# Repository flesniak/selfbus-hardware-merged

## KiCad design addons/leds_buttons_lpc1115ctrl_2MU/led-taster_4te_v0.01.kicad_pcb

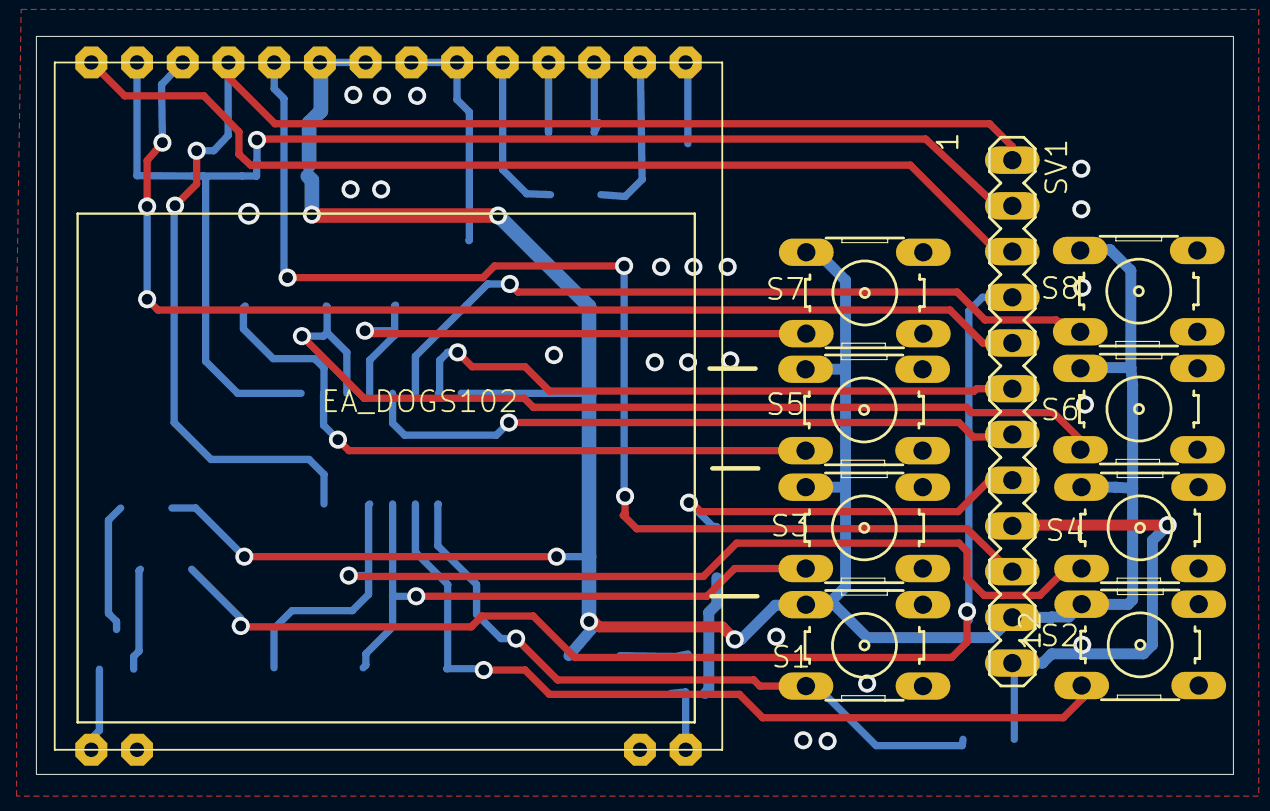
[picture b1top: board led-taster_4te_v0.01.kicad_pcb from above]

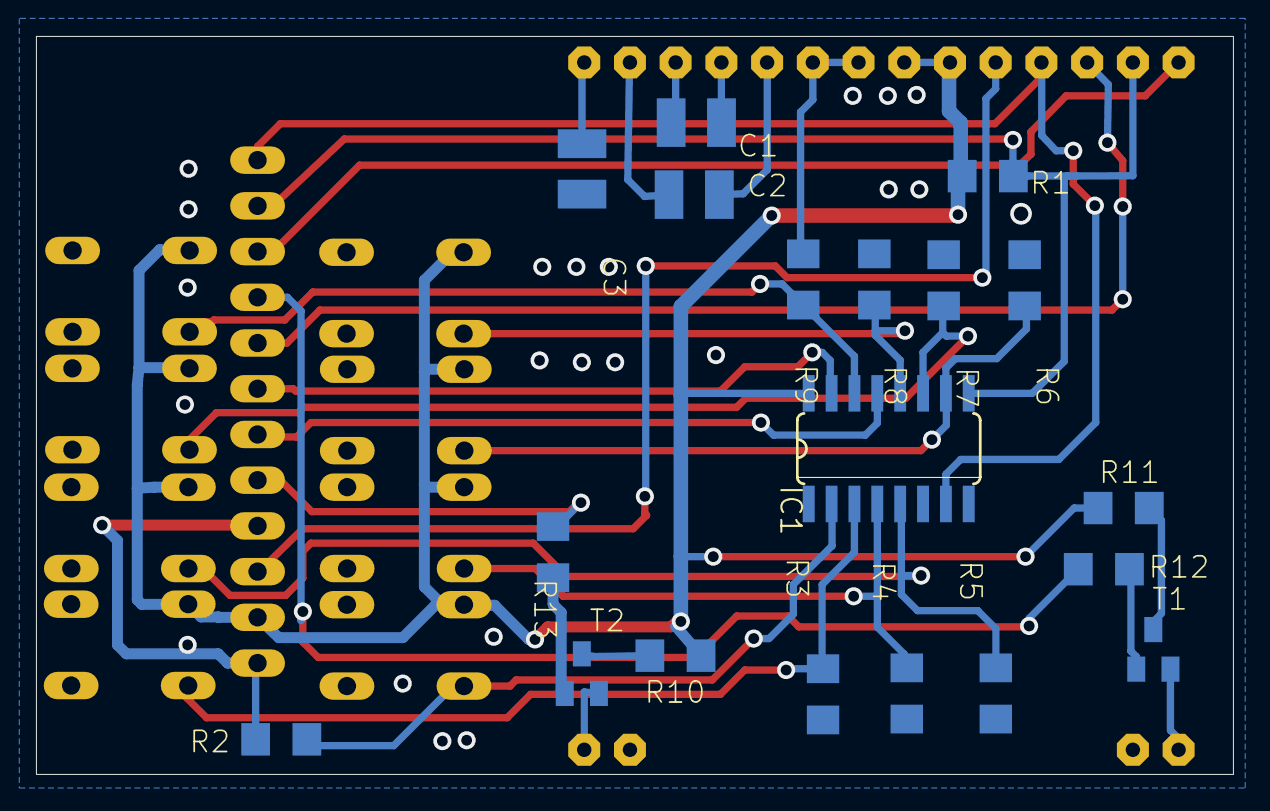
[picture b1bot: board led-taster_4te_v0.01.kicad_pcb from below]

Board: 2 copper layers, 66.5 x 41.0 mm, 29 parts (19 on the bottom side), 30 nets.

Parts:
C1, C2, C3: 1µ; C1210
EA_DOGS102: DOGS102
IC1: 74HC166D; SO16
R1, R2, R3, R4, R5, R6, R7, R8, R9: 10k; R1206
R10, R11: R1206
R12, R13: 1k; R1206
S1, S2, S3, S4, S5, S6, S7, S8: B3F-10XX
SV1: MA12-1
T1, T2: BC847; SOT23

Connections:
+3V3: EA_DOGS102.22, EA_DOGS102.23, IC1.16, R1.2, R10.1, R11.1, S1.1, S2.1, S3.1, S4.1, S5.1, S6.1, S7.1, S8.1, SV1.11
GND: C3.1, EA_DOGS102.2, EA_DOGS102.13, EA_DOGS102.20, EA_DOGS102.21, IC1.1, IC1.6, IC1.8, R2.2, R3.2, R4.2, R5.2, R6.2, R7.2, R8.2, R9.2, SV1.9, SV1.12
MISO: IC1.13, SV1.7
MOSI: EA_DOGS102.24, SV1.10
unnamed: IC1.2, R2.1, S1.3
unnamed: C2.2, EA_DOGS102.19
unnamed: C2.1, EA_DOGS102.16
unnamed: C1.2, EA_DOGS102.17
unnamed: C1.1, EA_DOGS102.18
unnamed: C3.2, EA_DOGS102.15
unnamed: IC1.3, R3.1, S2.3
unnamed: IC1.4, R4.1, S3.3
unnamed: IC1.5, R5.1, S4.3
unnamed: IC1.10, R6.1, S5.3
unnamed: IC1.14, R9.1, S8.3
unnamed: IC1.12, R8.1, S7.3
unnamed: IC1.11, R7.1, S6.3
unnamed: EA_DOGS102.28, SV1.3
unnamed: EA_DOGS102.1, T1.2
unnamed: EA_DOGS102.14, T2.2
unnamed: R10.2, T2.3
unnamed: R11.2, T1.3
unnamed: R13.1, T2.1
unnamed: R12.1, T1.1
unnamed: R12.2, SV1.4
unnamed: R13.2, SV1.8
unnamed: IC1.15, SV1.6
unnamed: EA_DOGS102.26, SV1.5
RESET: EA_DOGS102.27, IC1.9, R1.1, SV1.2
SCK: EA_DOGS102.25, IC1.7, SV1.1

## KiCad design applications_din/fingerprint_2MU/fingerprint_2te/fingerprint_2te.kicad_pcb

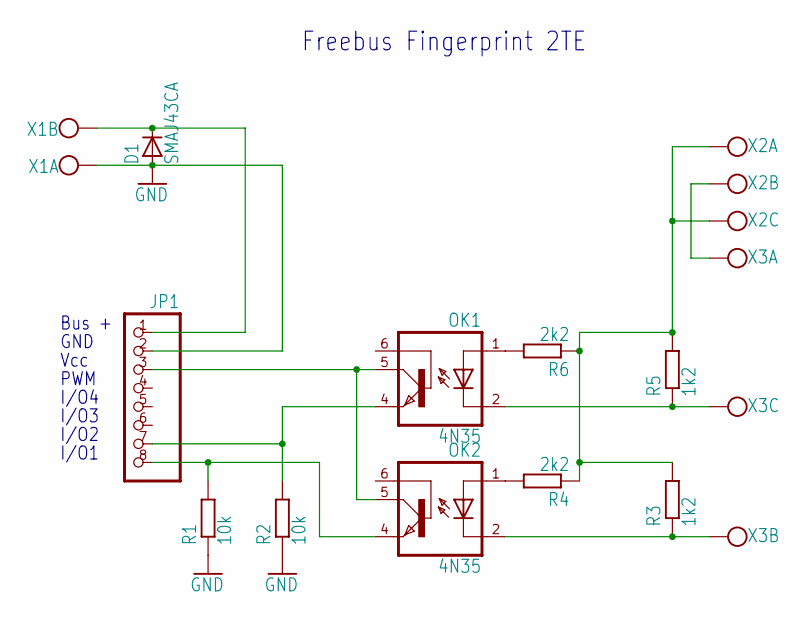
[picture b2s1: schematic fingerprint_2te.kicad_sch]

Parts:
D1: SMAJ43CA; SMA
JP1: PINHD-1X8; 1X08
OK1, OK2: 4N35; DIL06
R1, R2: 10k; 0207_10
R3, R5: 1k2; 0207_10
R4, R6: 2k2; 0207_10
X1: W237-02P; W237-132
X2, X3: W237-3E

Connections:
GND: D1.2 (A), JP1.2, R1.1, R2.1, X1.1
unnamed: JP1.8, OK2.4 (EMI), R1.2
unnamed: JP1.7, OK1.4 (EMI), R2.2
unnamed: JP1.3, OK1.5 (COL), OK2.5 (COL)
unnamed: D1.1 (C), JP1.1, X1.2
unnamed: OK2.1 (A), R4.2
unnamed: R3.2, R4.1, R5.2, R6.1, X2.1, X2.3
unnamed: X2.2, X3.1
unnamed: OK2.2 (C), R3.1, X3.2
unnamed: OK1.2 (C), R5.1, X3.3
unnamed: OK1.1 (A), R6.2

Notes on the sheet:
GND
PWM
Vcc
I/O2
Freebus Fingerprint 2TE
I/O4
I/O3
Bus +
I/O1

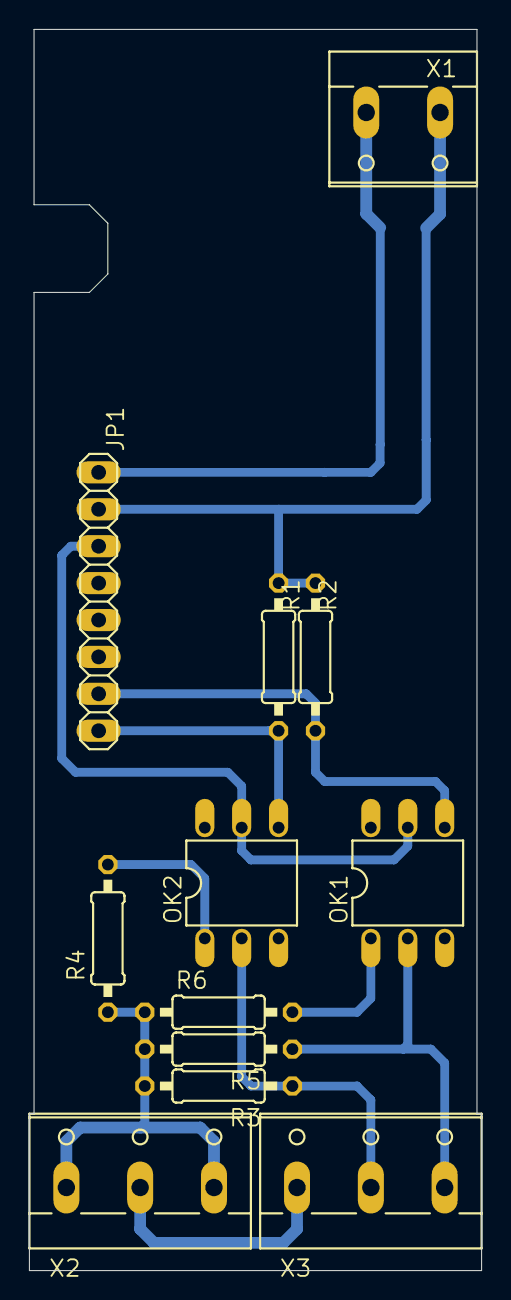
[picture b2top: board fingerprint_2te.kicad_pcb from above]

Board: 2 copper layers, 31.1 x 85.4 mm, 13 parts (1 on the bottom side), 11 nets.

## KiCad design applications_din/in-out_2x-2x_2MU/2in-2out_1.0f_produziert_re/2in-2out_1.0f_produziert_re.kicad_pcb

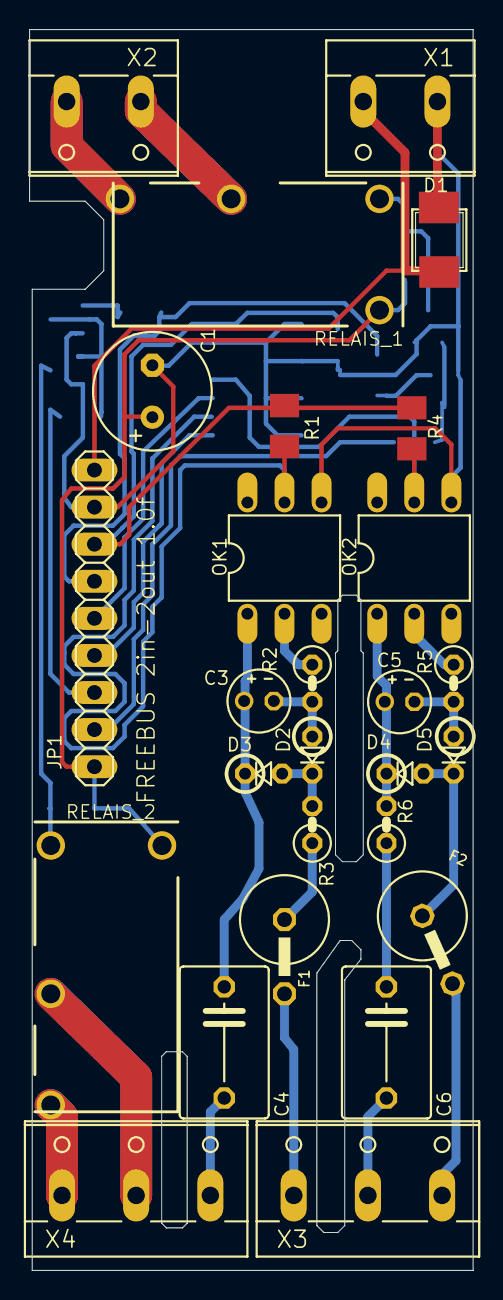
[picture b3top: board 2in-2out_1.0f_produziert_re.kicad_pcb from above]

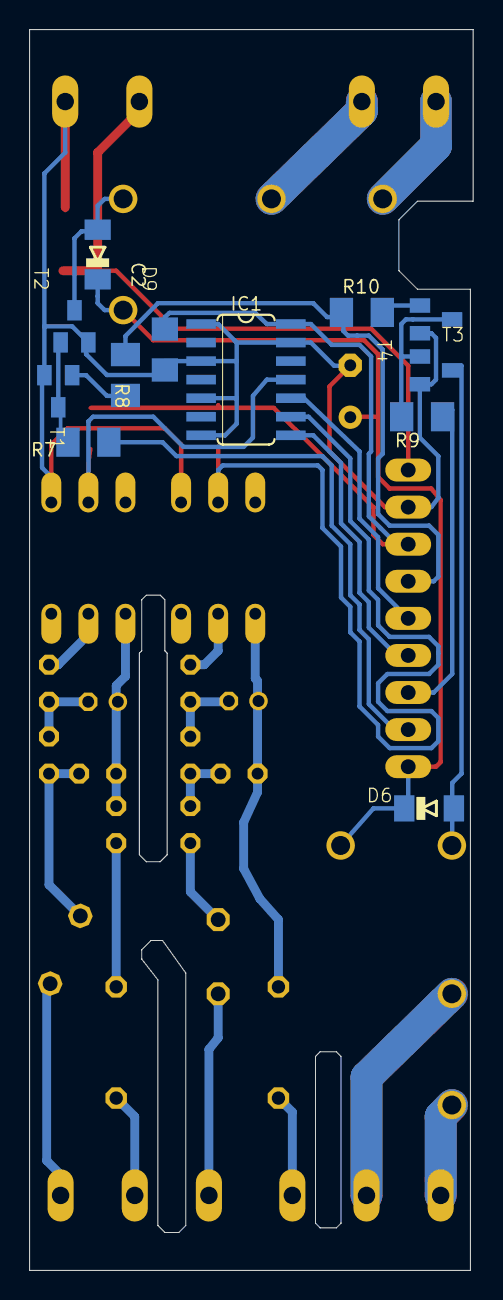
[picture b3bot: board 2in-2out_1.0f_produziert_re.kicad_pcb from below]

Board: 2 copper layers, 30.4 x 85.0 mm, 39 parts (12 on the bottom side), 35 nets.

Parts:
C1: 100µ; E3,5-8
C2: 100n; C1206
C3, C5: 10µ; E2-4
C4, C6: 47nF; C075-063X106
D1: SMAJ43CA; SMB
D2, D3, D4, D5: 1N4007; D-2.5
D6, D9: 1N4148; MINIMELF
F1, F2: 80mA; 0617V
IC1: 74HC14D; SO14
JP1: 1X09
OK1, OK2: CNY17-2; DIL06
R1, R4, R7, R8, R9, R10: 10k; M1206
R2, R5: 6k8; 0207_2V
R3, R6: 2k7 1W; 0207_2V
RELAIS_1, RELAIS_2: RE030024; RE-SCHRACK
T1, T2, T4: BC847; SOT23
T3: 847; SOT23
X1, X2: W237-132
X3, X4: W237-3E

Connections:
EIB+: D1.1, JP1.1, X1.2
GND: C1.-, C2.2, D1.2, IC1.1, IC1.3, IC1.5, IC1.7, IC1.13, JP1.2, OK1.4, OK2.4, T1.2, T2.2, T3.2, T4.2, X1.1
IO1: JP1.7, R9.2
IO2: JP1.8, R7.2
IO3: IC1.8, JP1.6
IO4: IC1.10, JP1.5
unnamed: OK1.2, R2.1
unnamed: RELAIS_1.11, X2.2
unnamed: C3.-, D2.A, R2.2
unnamed: D2.C, D3.A, R3.2
unnamed: RELAIS_1.14, X2.1
unnamed: F1.1, R3.1
unnamed: RELAIS_2.14, X4.2
unnamed: RELAIS_2.11, X4.1
unnamed: OK2.2, R5.1
unnamed: C6.1, R6.1
unnamed: F2.2, X3.3
unnamed: C5.-, D5.A, R5.2
unnamed: R7.1, T1.3, T2.1
unnamed: C4.2, X4.3
unnamed: R9.1, T3.3, T4.1
unnamed: D4.A, D5.C, F2.1
unnamed: D6.A, RELAIS_2.A1, T4.3
unnamed: C5.+, D4.C, OK2.1, R6.2
unnamed: R8.2, T1.1
unnamed: R10.2, T3.1
unnamed: C3.+, C4.1, D3.C, OK1.1
unnamed: C6.2, X3.2
unnamed: F1.2, X3.1
unnamed: IC1.11, OK2.5, R4.1
unnamed: IC1.9, OK1.5, R1.2
PWM: JP1.4, R8.1, R10.1
R3: D9.A, RELAIS_1.A1, T2.3
VCC: C2.1, IC1.14, JP1.3, R1.1, R4.2
VDD_IN: C1.+, D6.C, D9.C, JP1.9, RELAIS_1.A2, RELAIS_2.A2

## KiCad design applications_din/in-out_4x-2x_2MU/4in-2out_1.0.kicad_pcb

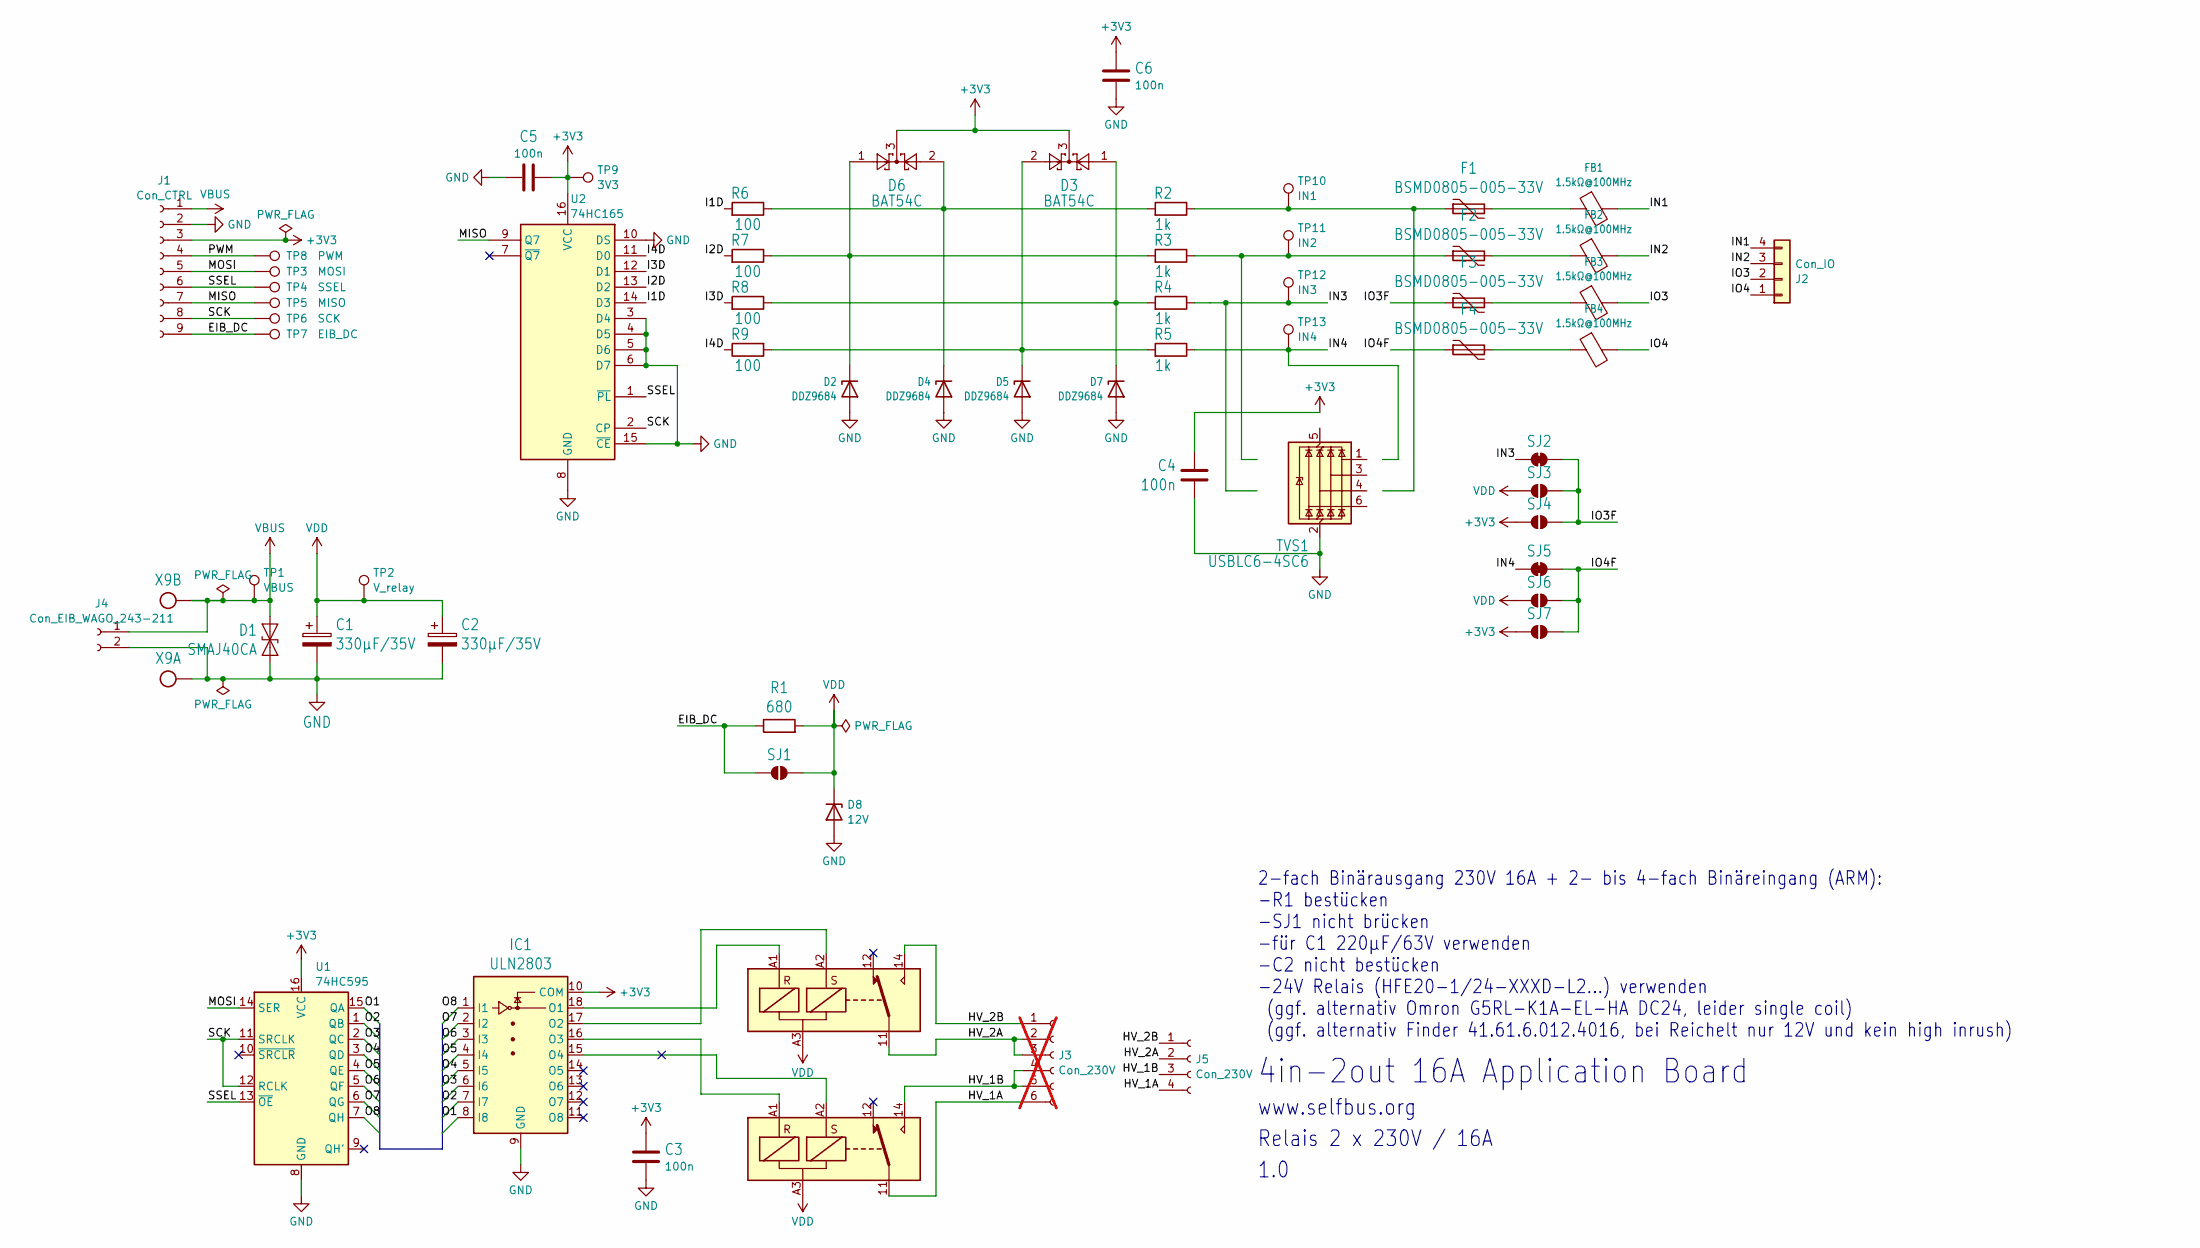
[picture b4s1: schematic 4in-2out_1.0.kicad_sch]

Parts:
C1, C2: 330µF/35V; CP_Radial_D8.0mm_P3.50mm
C3, C4, C5, C6: 100n; C_0805_2012Metric
D1: SMAJ40CA; D_SMA
D2, D4, D5, D7: DDZ9684; D_SOD-123
D3, D6: BAT54C; SOT-23
D8: 12V; D_MiniMELF
F1, F2, F3, F4: BSMD0805-005-33V; Fuse_0805_2012Metric
FB1, FB2, FB3, FB4: 1.5kΩ@100MHz; L_0805_2012Metric
IC1: ULN2803; SOIC-18W_7.5x11.6mm_P1.27mm
J1: Con_CTRL; PinHeader_1x09_P2.54mm_Vertical
J2: Con_IO; TerminalBlock_Phoenix_PT-1,5-4-3.5-H_1x04_P3.50mm_Horizontal
J3: Con_230V; TerminalBlock_Phoenix_MKDS-3-6-5.08_1x06_P5.08mm_Horizontal; not fitted
J4: Con_EIB_WAGO_243-211
J5: Con_230V; TerminalBlock_MetzConnect_Type701_RT11L03HGLU_1x04_P6.35mm_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
K1, K2: HFE20-1/24-1HSD-L2; HFE20-1-L2
R1: 680; R_1206_3216Metric
R2, R3, R4, R5: 1k; R_0805_2012Metric
R6, R7, R8, R9: 100; R_0805_2012Metric
SJ1: RELAY_24V; SolderJumper-2_P1.3mm_Open_Pad1.0x1.5mm
SJ2: IN3_INPUT; SolderJumper-2_P1.3mm_Open_Pad1.0x1.5mm
SJ3: IN3_VDD; SolderJumper-2_P1.3mm_Open_Pad1.0x1.5mm
SJ4: IN3_3V3; SolderJumper-2_P1.3mm_Open_Pad1.0x1.5mm
SJ5: IN4_INPUT; SolderJumper-2_P1.3mm_Open_Pad1.0x1.5mm
SJ6: IN4_VDD; SolderJumper-2_P1.3mm_Open_Pad1.0x1.5mm
SJ7: IN4_3V3; SolderJumper-2_P1.3mm_Open_Pad1.0x1.5mm
TP1: VBUS; TestPoint_Pad_D1.5mm
TP2: V_relay; TestPoint_Pad_D1.5mm
TP3: MOSI; TestPoint_Pad_D1.5mm
TP4: SSEL; TestPoint_Pad_D1.5mm
TP5: MISO; TestPoint_Pad_D1.5mm
TP6: SCK; TestPoint_Pad_D1.5mm
TP7: EIB_DC; TestPoint_Pad_D1.5mm
TP8: PWM; TestPoint_Pad_D1.5mm
TP9: 3V3; TestPoint_Pad_D1.5mm
TP10: IN1; TestPoint_Pad_D1.0mm
TP11: IN2; TestPoint_Pad_D1.0mm
TP12: IN3; TestPoint_Pad_D1.0mm
TP13: IN4; TestPoint_Pad_D1.0mm
TVS1: USBLC6-4SC6; SOT-23-6
U1: 74HC595; SOIC-16_3.9x9.9mm_P1.27mm
U2: 74HC165; SO-16_3.9x9.9mm_P1.27mm
X9: W237-102

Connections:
+3V3: C3.1, C4.2, C5.1, C6.1, D3.3, D6.3, IC1.10 (COM), J1.3, SJ4.1 (A), SJ7.1 (A), TP9.1, TVS1.5 (VBUS), U1.16 (VCC), U2.16 (VCC)
/EIB_DC: J1.9, R1.1, SJ1.1 (A), TP7.1
/HV_1A: J3.6, J5.4, K1.11
/HV_1B: J3.4, J3.5, J5.3, K1.14
/HV_2A: J3.2, J3.3, J5.2, K2.11
/HV_2B: J3.1, J5.1, K2.14
/I1D: R6.2, U2.14 (D3)
/I2D: R7.2, U2.13 (D2)
/I3D: R8.2, U2.12 (D1)
/I4D: R9.1, U2.11 (D0)
/IN1: FB1.2, J2.4
/IN2: FB2.2, J2.3
/IN3: R4.1, SJ2.1 (A), TP12.1, TVS1.6 (I/O4)
/IN4: R5.1, SJ5.1 (A), TP13.1, TVS1.1 (I/O1)
/IO3: FB3.2, J2.2
/IO3F: F3.1, SJ2.2 (B), SJ3.2 (B), SJ4.2 (B)
/IO4: FB4.2, J2.1
/IO4F: F4.1, SJ5.2 (B), SJ6.2 (B), SJ7.2 (B)
/MISO: J1.7, TP5.1, U2.9 (Q7)
/MOSI: J1.5, TP3.1, U1.14 (SER)
/O1: IC1.8 (I8), U1.15 (QA)
/O2: IC1.7 (I7), U1.1 (QB)
/O3: IC1.6 (I6), U1.2 (QC)
/O4: IC1.5 (I5), U1.3 (QD)
/O5: IC1.4 (I4), U1.4 (QE)
/O6: IC1.3 (I3), U1.5 (QF)
/O7: IC1.2 (I2), U1.6 (QG)
/O8: IC1.1 (I1), U1.7 (QH)
/PWM: J1.4, TP8.1
/SCK: J1.8, TP6.1, U1.11 (SRCLK), U1.12 (RCLK), U2.2 (CP)
/SSEL: J1.6, TP4.1, U1.13 (~OE), U2.1 (~PL)
GND: C1.2, C2.2, C3.2, C4.1, C5.2, C6.2, D1.1 (A1), D2.2 (A), D4.2 (A), D5.2 (A), D7.2 (A), D8.2 (A), IC1.9 (GND), J1.2, J4.2, TVS1.2 (GND), U1.8 (GND), U2.3 (D4), U2.4 (D5), U2.5 (D6), U2.6 (D7), U2.8 (GND), U2.10 (DS), U2.15 (~CE), X9.1 (KL)
unnamed: D2.1 (K), D6.1, R3.2, R7.1
unnamed: D4.1 (K), D6.2, R2.2, R6.1
unnamed: D3.2, D5.1 (K), R5.2, R9.2
unnamed: D3.1, D7.1 (K), R4.2, R8.1
unnamed: F1.2, FB1.1
unnamed: F2.2, FB2.1
unnamed: F3.2, FB3.1
unnamed: F4.2, FB4.1
unnamed: IC1.18 (O1), K2.A1
unnamed: IC1.17 (O2), K2.A2
unnamed: IC1.16 (O3), K1.A1
unnamed: IC1.15 (O4), K1.A2
VBUS: D1.2 (A2), J1.1, J4.1, TP1.1, X9.2 (KL)
VDD: C1.1, C2.1, D8.1 (K), K1.A3, K2.A3, R1.2, SJ1.2 (B), SJ3.1 (A), SJ6.1 (A), TP2.1

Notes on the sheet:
www.selfbus.org
4in-2out 16A Application Board
1.0
2-fach Binärausgang 230V 16A + 2- bis 4-fach Binäreingang (ARM): -R1 bestücken -SJ1 nicht brücken -für C1 220µF/63V verwenden -C2 nicht bestücken -24V Relais (HFE20-1/24-XXXD-L2...) verwenden (ggf. alternativ Omron G5RL-K1A-EL-HA DC24, leider single coil) (ggf. alternativ Finder 41.61.6.012.4016, b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
Relais 2 x 230V / 16A

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
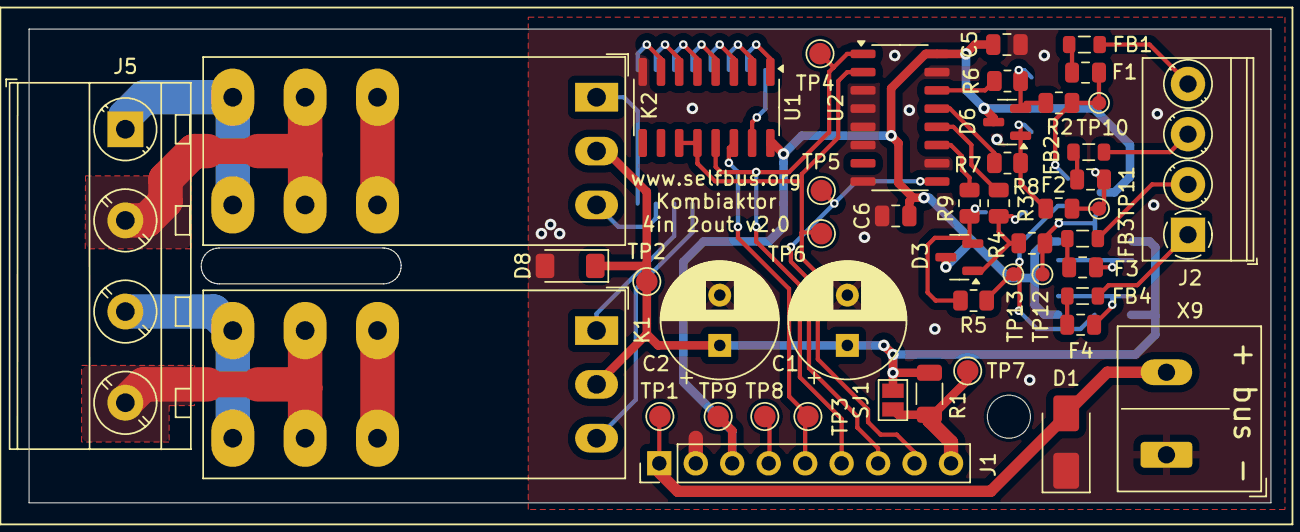
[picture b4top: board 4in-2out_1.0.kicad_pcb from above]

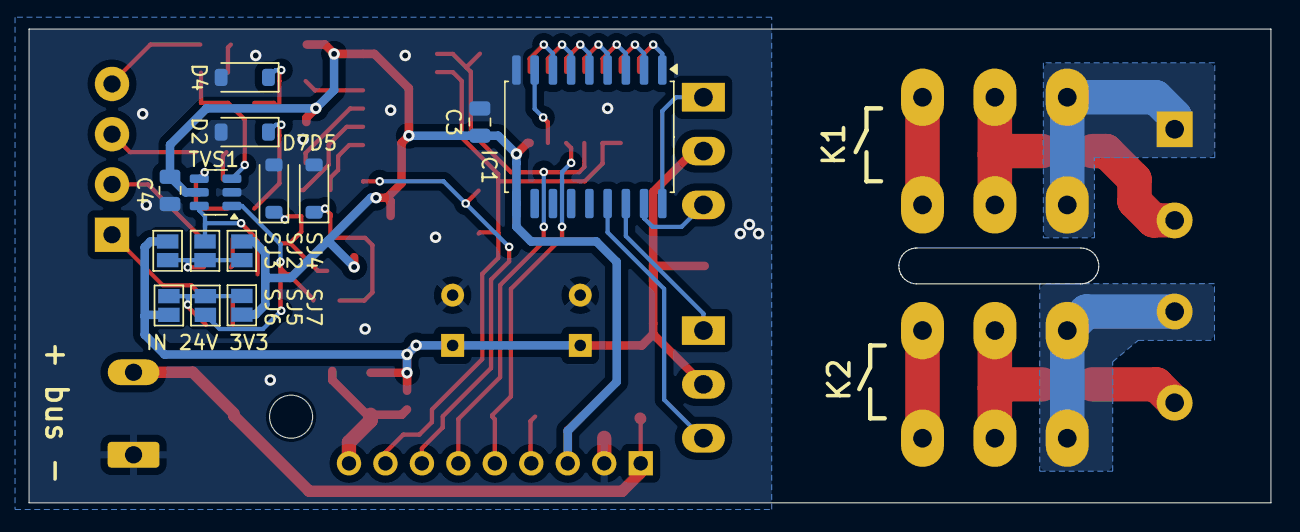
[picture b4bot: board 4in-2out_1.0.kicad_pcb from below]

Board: 2 copper layers, 86.5 x 33.0 mm, 62 parts (14 on the bottom side), 48 nets.

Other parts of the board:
HUT_CNMB_2: BOT; HUT_CNMB_2

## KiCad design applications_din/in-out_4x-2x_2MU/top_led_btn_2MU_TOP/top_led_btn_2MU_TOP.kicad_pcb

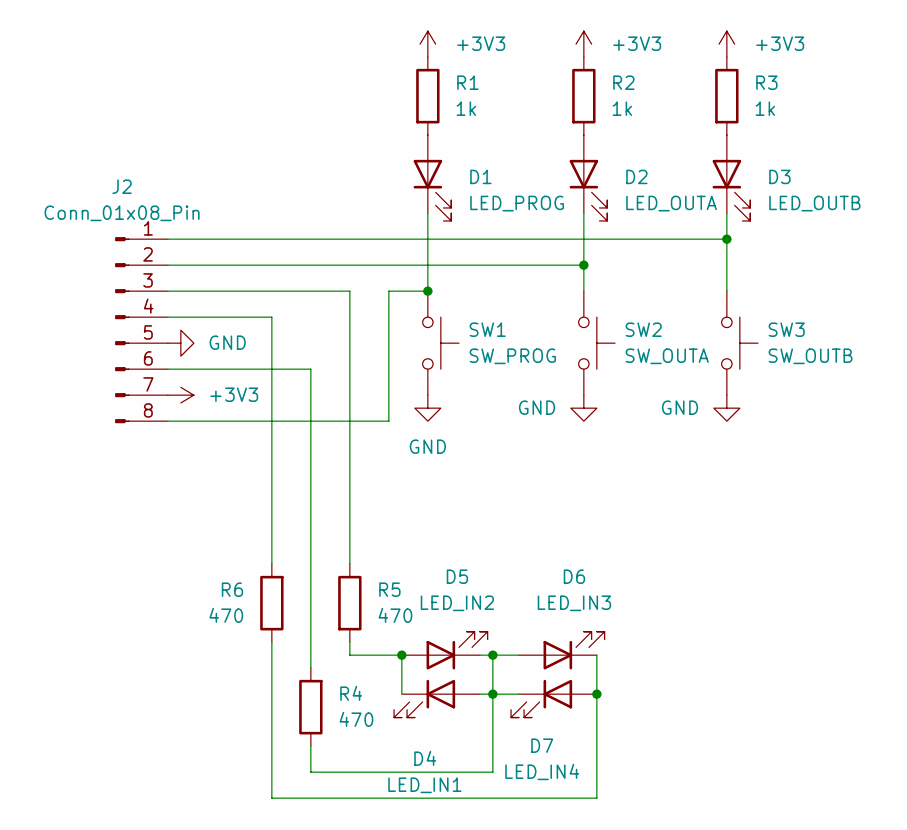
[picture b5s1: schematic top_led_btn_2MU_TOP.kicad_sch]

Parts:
D1: LED_PROG; LED_0805_2012Metric
D2: LED_OUTA; LED_0805_2012Metric
D3: LED_OUTB; LED_0805_2012Metric
D4: LED_IN1; LED_0805_2012Metric
D5: LED_IN2; LED_0805_2012Metric
D6: LED_IN3; LED_0805_2012Metric
D7: LED_IN4; LED_0805_2012Metric
J2: Conn_01x08_Pin; PinHeader_1x08_P2.54mm_Vertical
R1, R2, R3: 1k; R_0805_2012Metric
R4, R5, R6: 470; R_0805_2012Metric
SW1: SW_PROG; SW_SPST_CK_RS282G05A3
SW2: SW_OUTA; SW_SPST_CK_RS282G05A3
SW3: SW_OUTB; SW_SPST_CK_RS282G05A3

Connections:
+3V3: J2.7, R1.1, R2.1, R3.1
GND: J2.5, SW1.1, SW2.1, SW3.1
unnamed: D1.2 (A), R1.2
unnamed: D1.1 (K), J2.8, SW1.2
unnamed: D2.2 (A), R2.2
unnamed: D2.1 (K), J2.2, SW2.2
unnamed: D3.2 (A), R3.2
unnamed: D3.1 (K), J2.1, SW3.2
unnamed: D4.2 (A), D5.1 (K), D6.2 (A), D7.1 (K), R4.1
unnamed: D4.1 (K), D5.2 (A), R5.2
unnamed: D6.1 (K), D7.2 (A), R6.1
unnamed: J2.3, R5.1
unnamed: J2.4, R6.2
unnamed: J2.6, R4.2

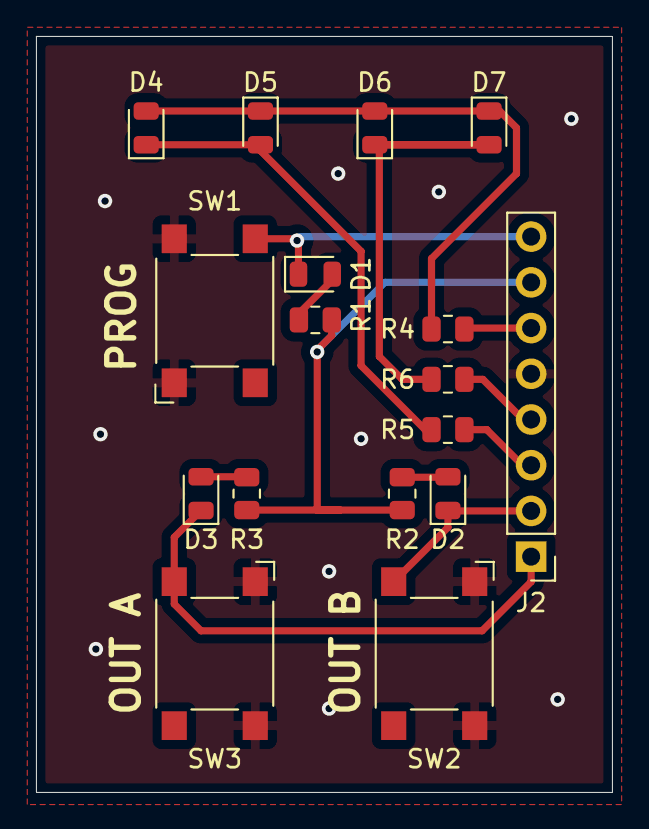
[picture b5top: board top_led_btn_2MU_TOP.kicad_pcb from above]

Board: 2 copper layers, 32.0 x 42.0 mm, 17 parts (0 on the bottom side), 14 nets.

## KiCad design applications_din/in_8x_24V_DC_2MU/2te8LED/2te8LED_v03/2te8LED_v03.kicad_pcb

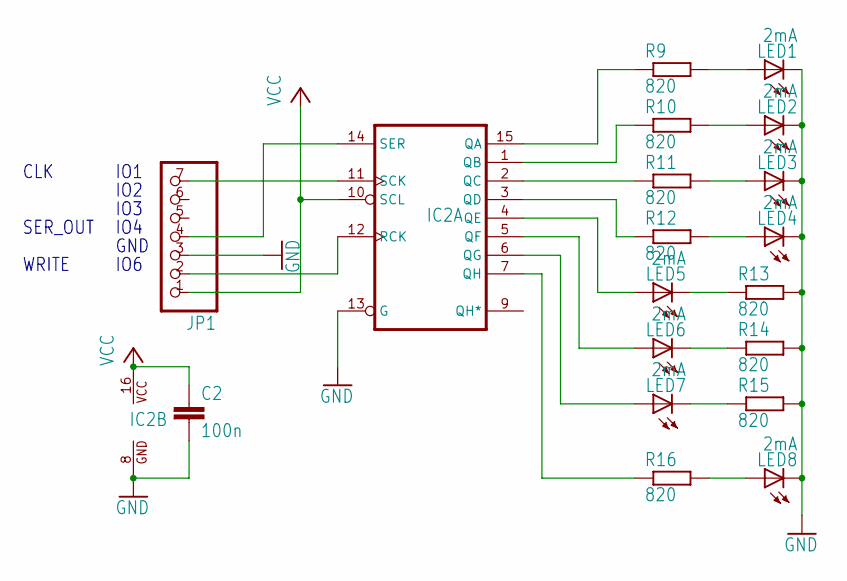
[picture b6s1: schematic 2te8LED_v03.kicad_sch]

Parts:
C2: 100n; C050-024X044
IC2: 74595D; SO16
JP1: PINHD-1X7_2.54; 1X07
LED1, LED2, LED3, LED4, LED5, LED6, LED7, LED8: 2mA; LED3MM
R9, R10, R11, R12, R13, R14, R15, R16: 820; 0204_7

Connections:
GND: C2.2, IC2.8 (GND), IC2.13 (G), JP1.3, LED1.K (C), LED2.K (C), LED3.K (C), LED4.K (C), LED8.K (C), R13.2, R14.2, R15.2
IO1: IC2.11 (SCK), JP1.7
IO4: IC2.14 (SER), JP1.4
IO6: IC2.12 (RCK), JP1.2
unnamed: IC2.15 (QA), R9.1
unnamed: IC2.1 (QB), R10.1
unnamed: IC2.2 (QC), R11.1
unnamed: IC2.3 (QD), R12.1
unnamed: IC2.4 (QE), LED5.A
unnamed: IC2.5 (QF), LED6.A
unnamed: IC2.6 (QG), LED7.A
unnamed: LED1.A, R9.2
unnamed: LED2.A, R10.2
unnamed: LED3.A, R11.2
unnamed: LED4.A, R12.2
unnamed: LED5.K (C), R13.1
unnamed: LED6.K (C), R14.1
unnamed: LED7.K (C), R15.1
unnamed: IC2.7 (QH), R16.1
unnamed: LED8.A, R16.2
VCC: C2.1, IC2.10 (SCL), IC2.16 (VCC), JP1.1

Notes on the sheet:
IO4
CLK
IO6
WRITE
GND
IO2
SER_OUT
IO3
IO1

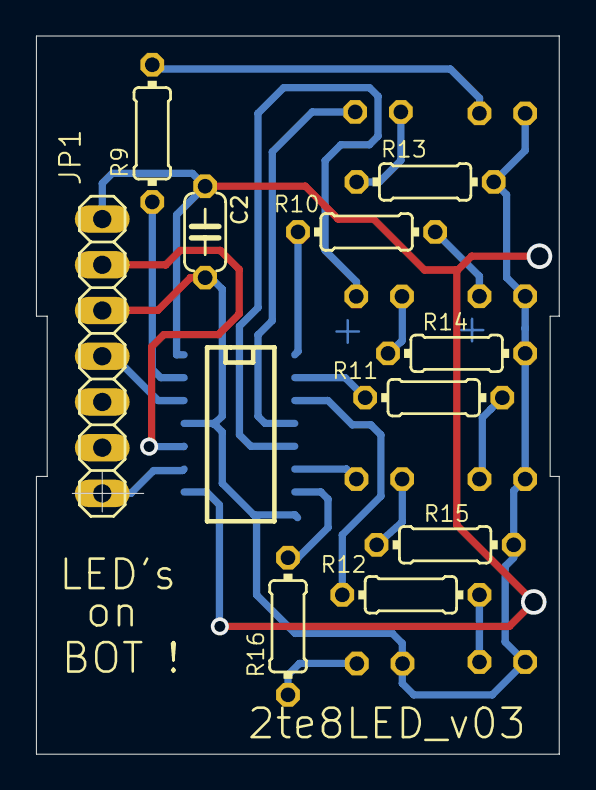
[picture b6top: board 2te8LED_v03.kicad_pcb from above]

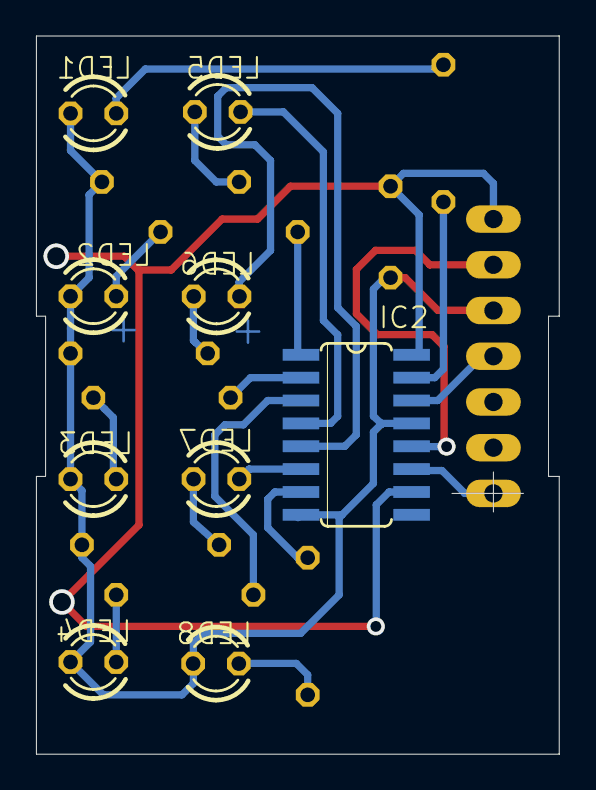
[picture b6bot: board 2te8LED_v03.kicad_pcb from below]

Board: 2 copper layers, 29.0 x 39.9 mm, 19 parts (9 on the bottom side), 21 nets.

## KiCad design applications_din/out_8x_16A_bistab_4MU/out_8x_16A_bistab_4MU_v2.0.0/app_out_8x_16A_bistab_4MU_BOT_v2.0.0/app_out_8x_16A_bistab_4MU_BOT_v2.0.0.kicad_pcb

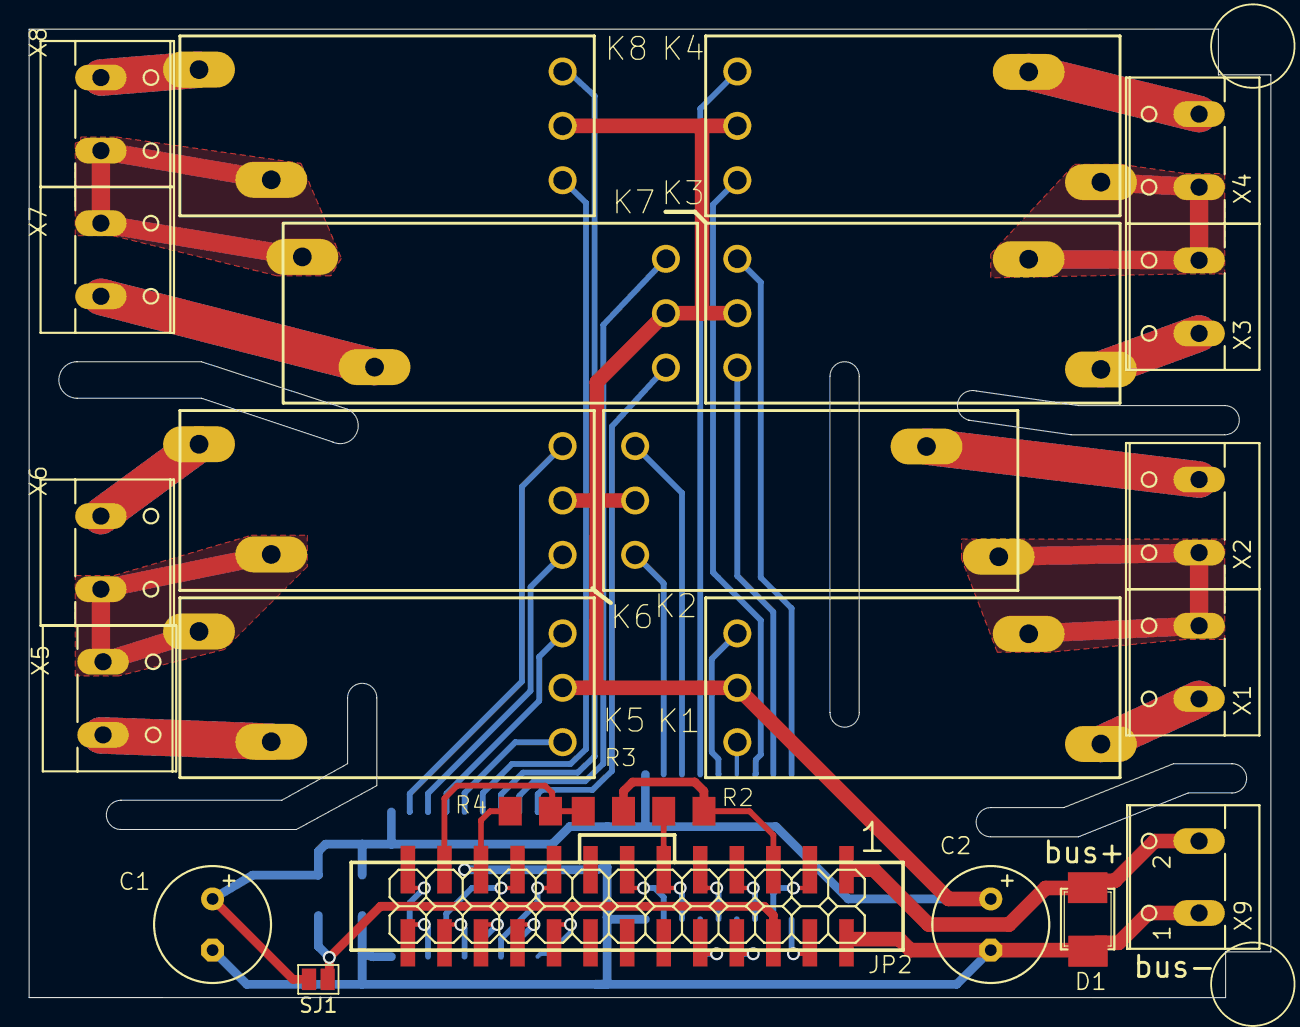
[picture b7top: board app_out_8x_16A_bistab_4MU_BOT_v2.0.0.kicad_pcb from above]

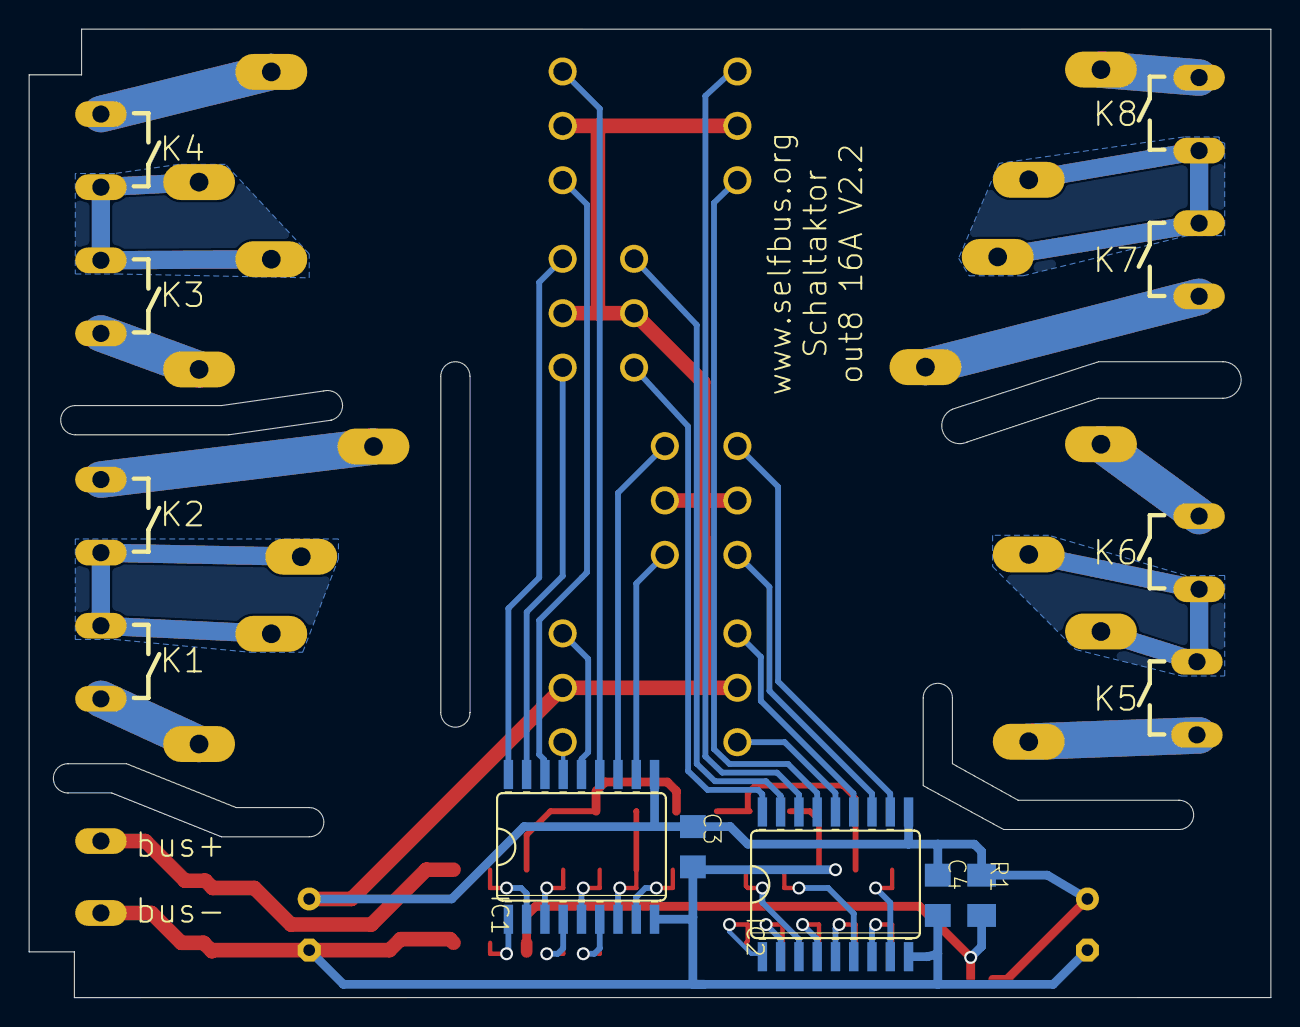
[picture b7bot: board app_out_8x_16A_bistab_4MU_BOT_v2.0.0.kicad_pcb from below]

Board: 2 copper layers, 86.3 x 67.3 mm, 31 parts (5 on the bottom side), 50 nets.

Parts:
C1, C2: 330µF/35V; E3,5-8
C3, C4: 100n; C1206
D1: SMAJ40CA; SMB
IC1, IC2: ULN2803; SO18W
JP2: A; 2X13SMD
K1, K2, K3, K4, K5, K6, K7, K8: HFE20-1-024-1HD504; HFE20-3-504
R1: 680; M1206
R2: 3k3; M1206
R3, R4: 33k; M1206
SJ1: A; SolderJumper-2_P1.3mm_Open_Pad1.0x1.5mm
U$1: HUT4C-NO-DRILL
X1, X2, X3, X4, X5, X6, X7, X8: W237-02P; W237-132
X9: W237-102

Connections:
+12V: D1.1 (C), JP2.1, X9.2 (KL)
/+3V3: JP2.5, R2.2, R3.2
/APP_SEL: JP2.23, R3.1, R4.2
/EIB_DC: JP2.6, R1.1, SJ1.1
/IO1: IC1.5 (I5), JP2.9
/IO2: IC1.4 (I4), JP2.8
/IO3: IC1.7 (I7), JP2.11, R2.1
/IO4: IC1.8 (I8), JP2.13
/IO5: IC1.1 (I1), JP2.4
/IO6: IC1.2 (I2), JP2.3
/IO7: IC1.6 (I6), JP2.10
/IO8: IC1.3 (I3), JP2.7
/IO9: IC2.5 (I5), JP2.24
/IO10: IC2.6 (I6), JP2.19
/IO11: IC2.7 (I7), JP2.26
/IO12: IC2.8 (I8), JP2.25
/IO13: IC2.1 (I1), JP2.18
/IO14: IC2.2 (I2), JP2.20
/IO15: IC2.4 (I4), JP2.22
/IO16: IC2.3 (I3), JP2.17
/O1: IC1.14 (O5), K1.2 (S+)
/O2: IC1.15 (O4), K1.1 (R+)
/O3: IC1.12 (O7), K2.2 (S+)
/O4: IC1.11 (O8), K2.1 (R+)
/O5: IC1.18 (O1), K3.2 (S+)
/O6: IC1.17 (O2), K3.1 (R+)
/O7: IC1.13 (O6), K4.2 (S+)
/O8: IC1.16 (O3), K4.1 (R+)
/O9: IC2.14 (O5), K5.2 (S+)
/O10: IC2.13 (O6), K5.1 (R+)
/O11: IC2.12 (O7), K6.2 (S+)
/O12: IC2.11 (O8), K6.1 (R+)
/O13: IC2.18 (O1), K7.2 (S+)
/O14: IC2.17 (O2), K7.1 (R+)
/O15: IC2.15 (O4), K8.2 (S+)
/O16: IC2.16 (O3), K8.1 (R+)
GND: C1.-, C2.-, C3.2, C4.2, D1.2 (A), IC1.9 (GND), IC2.9 (GND), JP2.2, JP2.21, R4.1, X9.1 (KL)
unnamed: K1.14B (PA), X1.1 (KL)
unnamed: K1.11A (PB), K2.14B (PA), X1.2 (KL), X2.1 (KL)
unnamed: K2.11A (PB), X2.2 (KL)
unnamed: K3.14B (PA), X3.1 (KL)
unnamed: K3.11A (PB), K4.14B (PA), X3.2 (KL), X4.1 (KL)
unnamed: K4.11A (PB), X4.2 (KL)
unnamed: K5.14B (PA), K6.11A (PB), X5.1 (KL), X6.2 (KL)
unnamed: K5.11A (PB), X5.2 (KL)
unnamed: K6.14B (PA), X6.1 (KL)
unnamed: K7.14B (PA), K8.11A (PB), X7.1 (KL), X8.2 (KL)
unnamed: K7.11A (PB), X7.2 (KL)
unnamed: K8.14B (PA), X8.1 (KL)
VDD: C1.+, C2.+, C3.1, C4.1, IC1.10 (CD+), IC2.10 (CD+), K1.5 (-), K2.5 (-), K3.5 (-), K4.5 (-), K5.5 (-), K6.5 (-), K7.5 (-), K8.5 (-), R1.2, SJ1.2
